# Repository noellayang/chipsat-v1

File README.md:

# ChipSat v1: Solar-Powered CubeSat Power Testbed

ChipSat v1 is a custom 45mm x 45mm PCB I built to test how firmware power-management decisions affect the actual current draw of a small satellite-style system. It was developed alongside my power budget work for the Duke Solar Sail project.

## What this is

The goal was not to reproduce flight hardware exactly. Instead, I wanted a physical testbed where I could keep the hardware fixed and measure how much the power draw changed as I switched between different firmware schedules.

The board includes:

* ESP32-C3-MINI-1 MCU with native USB
* Solar input and Li-ion charging using the BQ25185
* Two INA219 current and voltage monitors: one on the solar input and one on the main system rail
* ICM-42688-P 6-axis IMU over SPI
* VEML7700 ambient light sensor
* Switchable `+3V3_SENS` rail for the sensor domain
* 36Ω switched load behind a solder jumper to emulate an approximately 300mW ADCS load, comparable to a single magnetorquer actuation
* BLE telemetry using the ESP32-C3 radio as a stand-in for LoRa downlink. I kept the same 780ms transmission window and cadence used in the mission power model (and without attempting to reproduce LoRa RF behavior)

## Repo layout

```text
hardware/         KiCad project: schematic, PCB layout, design rules
manufacturing/    Gerbers, drill files, pick-and-place, fab submission files
images/           Board photos and test figures
docs/             BOM
```

## Firmware power states

| State         | MCU                       | IMU | +3V3_SENS | BLE proxy                           | Mission interpretation                                   |
| ------------- | ------------------------- | --- | --------- | ----------------------------------- | -------------------------------------------------------- |
| Eclipse sleep | Deep sleep between events | Off | Off       | Wake every 30s, advertise for 0.78s | Earth-shadow stress case with nominal telemetry retained |
| Housekeeping  | Active                    | Off | Off       | 0.78s every 30s                     | Scheduling and health checks                             |
| Full sensing  | Active                    | On  | On        | 0.78s every 30s                     | Complete sensing window                                  |

## Results

### Power-state testing

Deep sleep reduced average current by 95.4%.

Each state was run over a representative 30s cycle:

* Eclipse sleep: 2.25mA
* Housekeeping: 48.59 ± 0.10mA
* Full sensing: 50.14 ± 0.11mA

I also tested the switched 36Ω load used to emulate an ADCS event. System current increased from a 26.02mA baseline to 118.48 ± 0.87mA with the load enabled, close to the expected result for an approximately 300mW resistive load.

### BLE telemetry

I held the board in Full Sensing for 60s and enabled BLE advertising for 780ms every 30s.

Across three trials, the baseline stayed at 53.67 ± 0.10mA. During the advertising windows, the INA219 measured short peaks up to 121.5mA.

At this cadence, the radio is active for roughly 2.6% of the cycle. The test helped confirm that the BLE event appears as a short current spike rather than setting the power draw for the full operating period.

### Solar harvesting

I used the solar-side INA219 together with the VEML7700 to compare harvested power against measured illuminance.

Harvested power increased from 3.01 ± 0.68mW at about 1669 lux to 16.77 ± 0.91mW at about 2669 lux.

The lowest-light measurement is close to the practical measurement floor of the INA219 with the 0.1Ω shunt, so that point has noticeably more variation than the higher-light measurements.

## Bring-up notes

A few issues from bring-up ended up being especially useful:

### I2C bus switching

The ESP32-C3 only has one I2C controller, while the board uses two physical I2C buses. Firmware therefore remaps the controller depending on which bus is being accessed.

One issue appeared when I disabled the sensor rail before an I2C transaction had fully completed. This could leave SDA or SCL in the wrong state and break later communication. I fixed it by completing the transaction and releasing the bus before switching off `+3V3_SENS`.

### Low-current measurement floor

Under weak illumination, the solar current became small enough that the INA219 and 0.1Ω shunt were operating near their useful measurement limit. At that point, offset and resolution were large enough for the reported current to occasionally drift around zero.

I kept the data rather than filtering it out, but marked the lowest-light point as being close to the measurement floor.

### BLE stack overhead

One result I did not initially expect was the cost of simply initializing BLE.

Even with advertising disabled, bringing up the BLE stack raised the active current noticeably. Because of this, "advertising off" and "BLE fully deinitialized" are separate power states in the firmware rather than being treated as equivalent.

## Manufacturing

Gerbers, drill files, and the original fab submission files for the 2-layer PCB are included in [`manufacturing/`](manufacturing/).

The KiCad project is the source of truth. If you need outputs for a different board house, regenerate them from:

`hardware/chipsat_v1.kicad_pcb`

## BOM

The full bill of materials, including LCSC part numbers, is available at [`docs/BOM.csv`](docs/BOM.csv).

## Opening the project

KiCad 8 or newer is recommended.

Open:

`hardware/chipsat_v1.kicad_pro`

## License

MIT. See [LICENSE](LICENSE).

The hardware design files are included for reference and reuse. If you build directly on the board design, credit back to this repo is appreciated.

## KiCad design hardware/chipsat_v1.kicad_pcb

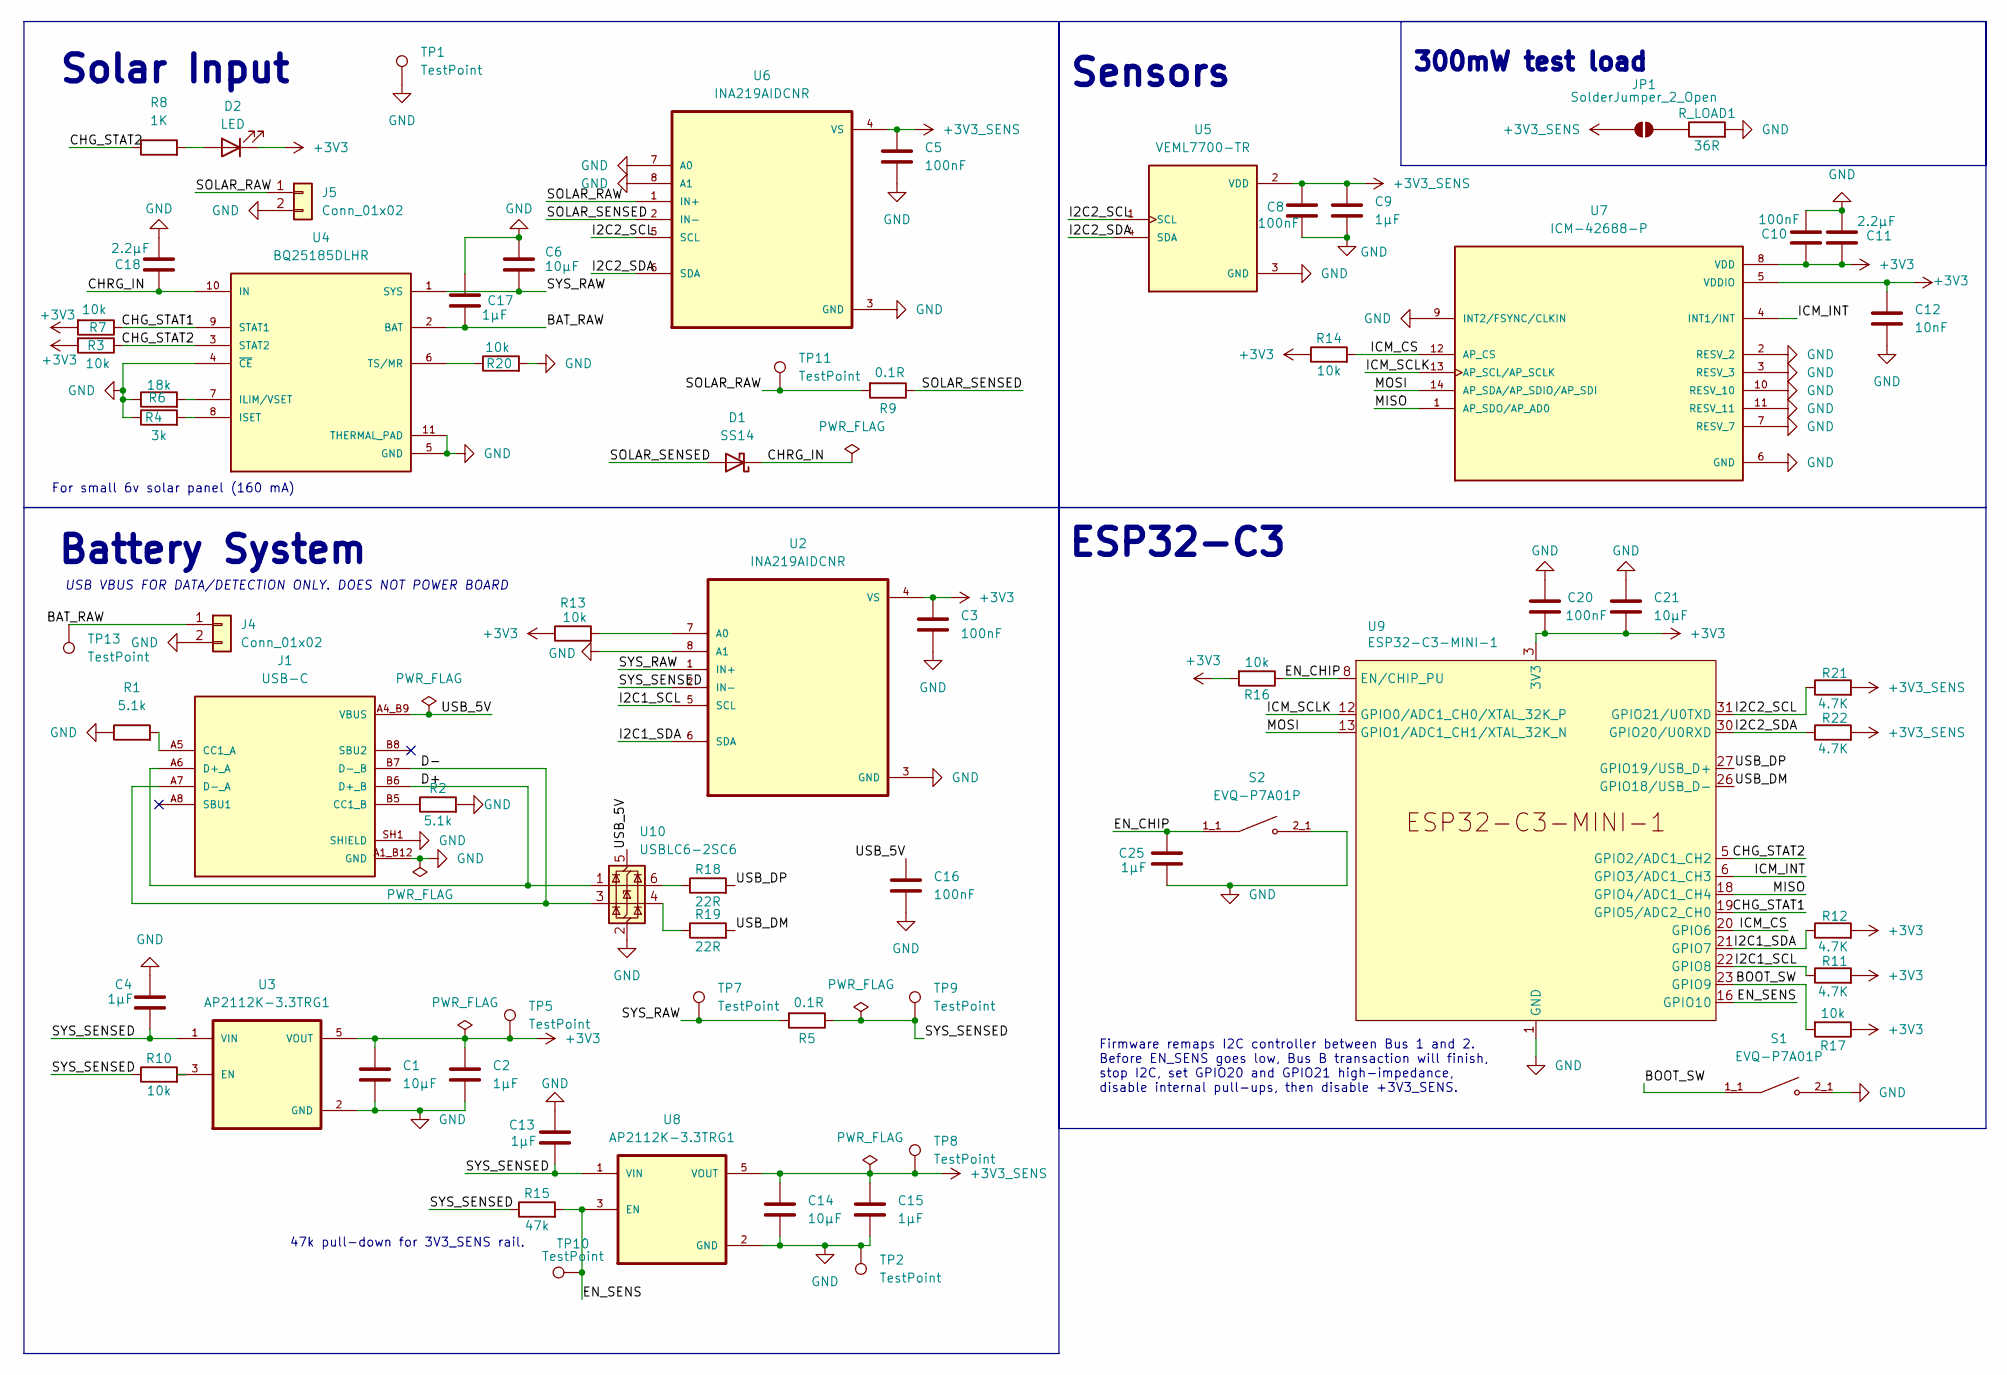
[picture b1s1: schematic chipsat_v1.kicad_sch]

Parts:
C1, C6, C14, C21: 10µF; C_0805_2012Metric; Manufacturer Part Number CL21A106KPFNNNE; LCSC Part # C17024
C2, C4, C9, C13, C15, C17, C25: 1µF; C_0603_1608Metric; Manufacturer Part Number CL10A105KP8NNNC; LCSC Part # C26413
C3, C5, C8, C10, C16, C20: 100nF; C_0603_1608Metric; Manufacturer Part Number CL10B104KB8NNNC; LCSC Part # C1591
C11, C18: 2.2µF; C_0805_2012Metric; Manufacturer Part Number CL21A225KPFNNNE; LCSC Part # C84716
C12: 10nF; C_0603_1608Metric; Manufacturer Part Number CL10B103KB8NNNC; LCSC Part # C1589
D1: SS14; D_SMA; Manufacturer Part Number SS14; LCSC Part # C2480
D2: LED; LED_0603_1608Metric; Manufacturer Part Number KT-0603R; LCSC Part # C2286
J1: USB-C; AMPHENOL_12402012E212A; PARTREV 4; LCSC Part # C5150972
J4, J5: Conn_01x02; JST_XH_B2B-XH-A_1x02_P2.50mm_Vertical; Manufacturer Part Number B2B-XH-A(LF)(SN); LCSC Part # C158012
JP1: SolderJumper_2_Open; SolderJumper-2_P1.3mm_Open_RoundedPad1.0x1.5mm
R1, R2: 5.1k; R_0603_1608Metric; Manufacturer Part Number 0603WAF5101T5E; LCSC Part # C23186
R3, R7, R10, R13, R14, R16, R17, R20: 10k; R_0603_1608Metric; Manufacturer Part Number 0603WAF1002T5E; LCSC Part # C25804
R4: 3k; R_0603_1608Metric; Manufacturer Part Number 0603WAF3001T5E; LCSC Part # C4211
R5, R9: 0.1R; R_1206_3216Metric; Manufacturer Part Number RE1206F1R100; LCSC Part # C46961734
R6: 18k; R_0603_1608Metric; Manufacturer Part Number 0603WAF1802T5E; LCSC Part # C25810
R8: 1K; R_0603_1608Metric; Manufacturer Part Number RC0603FR-071KL; LCSC Part # C22548
R11, R12, R21, R22: 4.7K; R_0603_1608Metric; Manufacturer Part Number 0603WAF4701T5E; LCSC Part # C23162
R15: 47k; R_0603_1608Metric; Manufacturer Part Number 0603WAF4702T5E; LCSC Part # C25819
R18, R19: 22R; R_0603_1608Metric; Manufacturer Part Number 0603WAF220JT5E; LCSC Part # C23345
R_LOAD1: 36R; R_2512_6332Metric; Manufacturer Part Number 25121WF360JT4E; LCSC Part # C190228
S1, S2: EVQ-P7A01P; SW_EVQ-P7A01P; PARTREV 2022.4; LCSC Part # C79167
TP1, TP2, TP5, TP7, TP8, TP9, TP11, TP13: TestPoint; TP_SMD_Round_1.5mm
TP10: TestPoint; TP_SMD_Round_1.2mm
U2, U6: INA219AIDCNR; SOT65P280X145-8N; Manufacturer Part Number INA219AIDCNR; LCSC Part # C87469
U3, U8: AP2112K-3.3TRG1; SOT95P285X140-5N; PARTREV 2-2; LCSC Part # C51118
U4: BQ25185DLHR; IC_BQ25185DLHR; PARTREV OCTOBER 2023; LCSC Part # C19725033
U5: VEML7700-TR; XDCR_VEML7700-TR; PARTREV 1.6; LCSC Part # C504893
U7: ICM-42688-P; PQFN50P300X250X97-14N; PARTREV 1.2; LCSC Part # C1850418
U9: ESP32-C3-MINI-1; Manufacturer Part Number ESP32-C3-MINI-1-N4; LCSC Part # C2838502
U10: USBLC6-2SC6; SOT-23-6; Manufacturer Part Number USBLC6-2SC6; LCSC Part # C7519

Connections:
+3V3: C1.1, C2.2, C3.1, C10.1, C11.1, C12.1, C20.2, C21.2, D2.1 (K), R3.2, R7.2, R11.2, R12.2, R13.1, R14.1, R16.2, R17.1, TP5.1 (1_1), U2.4 (VS), U3.5 (VOUT), U7.5 (VDDIO), U7.8 (VDD), U9.3 (3V3)
+3V3_SENS: C5.1, C8.2, C9.2, C14.2, C15.2, JP1.1 (A), R21.2, R22.2, TP8.1 (1_1), U5.2 (VDD), U6.4 (VS), U8.5 (VOUT)
/BAT_RAW: C17.1, J4.1, TP13.1 (1_1), U4.2 (BAT)
/BOOT_SW: R17.2, S1.1_1, S1.1_2, U9.23 (GPIO9)
/CHG_STAT1: R7.1, U4.9 (STAT1), U9.19 (GPIO5/ADC2_CH0)
/CHG_STAT2: R3.1, R8.1, U4.3 (STAT2), U9.5 (GPIO2/ADC1_CH2)
/CHRG_IN: C18.1, D1.1 (K), U4.10 (IN)
/D+: J1.A6 (D+_A), J1.B6 (D+_B), U10.1 (I/O1)
/D-: J1.A7 (D-_A), J1.B7 (D-_B), U10.3 (I/O2)
/EN_CHIP: C25.2, R16.1, S2.1_1, S2.1_2, U9.8 (EN/CHIP_PU)
/EN_SENS: R15.2, TP10.1 (1_1), U8.3 (EN), U9.16 (GPIO10)
/I2C1_SCL: R11.1, U2.5 (SCL), U9.22 (GPIO8)
/I2C1_SDA: R12.1, U2.6 (SDA), U9.21 (GPIO7)
/I2C2_SCL: R21.1, U5.1 (SCL), U6.5 (SCL), U9.31 (GPIO21/U0TXD)
/I2C2_SDA: R22.1, U5.4 (SDA), U6.6 (SDA), U9.30 (GPIO20/U0RXD)
/ICM_CS: R14.2, U7.12 (AP_CS), U9.20 (GPIO6)
/ICM_INT: U7.4 (INT1/INT), U9.6 (GPIO3/ADC1_CH3)
/ICM_SCLK: U7.13 (AP_SCL/AP_SCLK), U9.12 (GPIO0/ADC1_CH0/XTAL_32K_P)
/MISO: U7.1 (AP_SDO/AP_AD0), U9.18 (GPIO4/ADC1_CH4)
/MOSI: U7.14 (AP_SDA/AP_SDIO/AP_SDI), U9.13 (GPIO1/ADC1_CH1/XTAL_32K_N)
/SOLAR_RAW: J5.1, R9.2, TP11.1 (1_1), U6.1 (IN+)
/SOLAR_SENSED: D1.2 (A), R9.1, U6.2 (IN-)
/SYS_RAW: C6.2, R5.2, TP7.1 (1_1), U2.1 (IN+), U4.1 (SYS)
/SYS_SENSED: C4.1, C13.1, R5.1, R10.1, R15.1, TP9.1 (1_1), U2.2 (IN-), U3.1 (VIN), U8.1 (VIN)
/USB_DM: R19.2, U9.26 (GPIO18/USB_D-)
/USB_DP: R18.2, U9.27 (GPIO19/USB_D+)
GND: C1.2, C2.1, C3.2, C4.2, C5.2, C6.1, C8.1, C9.1, C10.2, C11.2, C12.2, C13.2, C14.1, C15.1, C16.1, C17.2, C18.2, C20.1, C21.1, C25.1, J1.A1_B12 (GND), J1.B1_A12 (GND), J1.SH1 (SHIELD), J1.SH2 (SHIELD), J1.SH3 (SHIELD), J1.SH4 (SHIELD), J4.2, J5.2, R1.1, R2.2, R4.1, R6.1, R20.2, R_LOAD1.2, S1.2_1, S1.2_2, S2.2_1, S2.2_2, TP1.1 (1_1), TP2.1 (1_1), U2.3 (GND), U2.8 (A1), U3.2 (GND), U4.4 (~CE), U4.5 (GND), U4.11 (THERMAL_PAD), U5.3 (GND), U6.3 (GND), U6.7 (A0), U6.8 (A1), U7.2 (RESV_2), U7.3 (RESV_3), U7.6 (GND), U7.7 (RESV_7), U7.9 (INT2/FSYNC/CLKIN), U7.10 (RESV_10), U7.11 (RESV_11), U8.2 (GND), U9.1 (GND), U9.2 (GND), U9.11 (GND), U9.14 (GND), U9.36 (GND), U9.37 (GND), U9.38 (GND), U9.39 (GND), U9.40 (GND), U9.41 (GND), U9.42 (GND), U9.43 (GND), U9.44 (GND), U9.45 (GND), U9.46 (GND), U9.47 (GND), U9.48 (GND), U9.49 (GND), U9.50 (GND), U9.51 (GND), U9.52 (GND), U9.53 (GND), U10.2 (GND)
unnamed: D2.2 (A), R8.2
unnamed: J1.A5 (CC1_A), R1.2
unnamed: J1.B5 (CC1_B), R2.1
unnamed: JP1.2 (B), R_LOAD1.1
unnamed: R18.1, U10.6 (I/O1)
unnamed: R19.1, U10.4 (I/O2)
unnamed: R13.2, U2.7 (A0)
unnamed: R10.2, U3.3 (EN)
unnamed: R6.2, U4.7 (ILIM/VSET)
unnamed: R4.2, U4.8 (ISET)
unnamed: R20.1, U4.6 (TS/MR)
VBUS: C16.2, J1.A4_B9 (VBUS), J1.B4_A9 (VBUS), U10.5 (VBUS)

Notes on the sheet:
ESP32-C3
47k pull-down for 3V3_SENS rail.
Firmware remaps I2C controller between Bus 1 and 2. Before EN_SENS goes low, Bus B transaction will finish, stop I2C, set GPIO20 and GPIO21 high-impedance, disable internal pull-ups, then disable +3V3_SENS.
USB VBUS FOR DATA/DETECTION ONLY. DOES NOT POWER BOARD
300mW test load
Battery System
Solar Input
For small 6v solar panel (160 mA)
Sensors

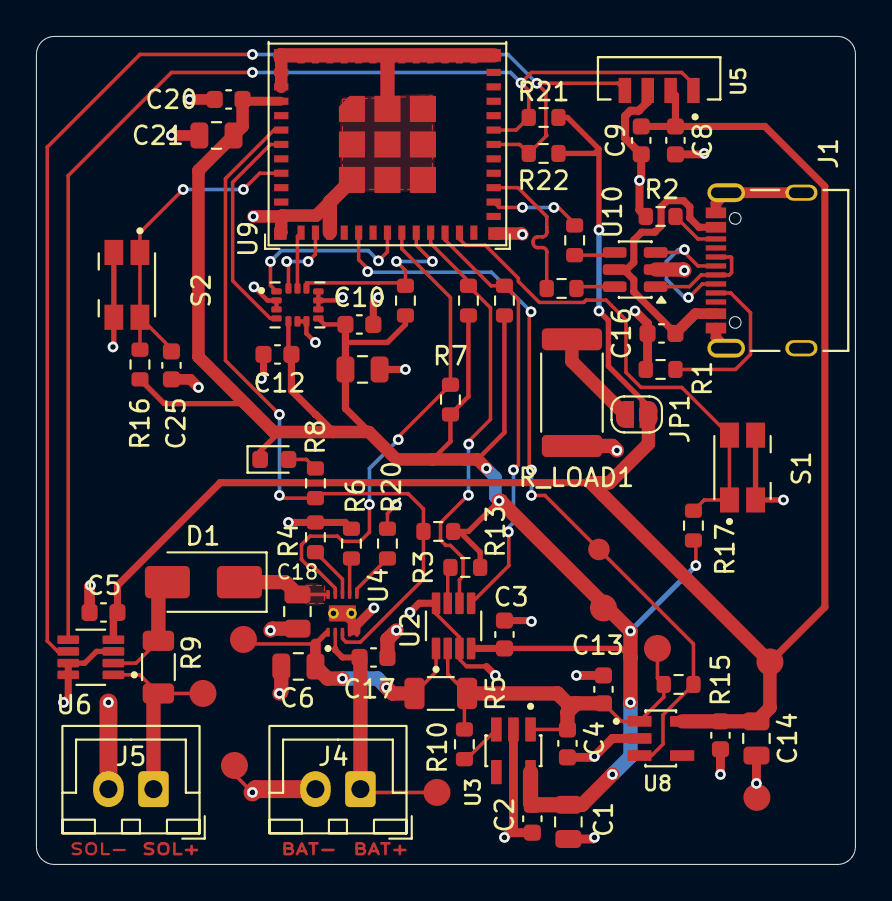
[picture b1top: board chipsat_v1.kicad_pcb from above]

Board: 2 copper layers, 45.5 x 46.0 mm, 69 parts (0 on the bottom side), 39 nets.

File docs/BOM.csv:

"Designator","Qty","Comment","Footprint","LCSC Part #","Manufacturer","Manufacturer Part Number"
"C1,C6,C14,C21","4","10µF","Capacitor_SMD:C_0805_2012Metric","C17024","Samsung Electro-Mechanics","CL21A106KPFNNNE"
"C2,C4,C9,C13,C15,C17,C25","7","1µF","Capacitor_SMD:C_0603_1608Metric","C26413","Samsung Electro-Mechanics","CL10A105KP8NNNC"
"C3,C5,C8,C10,C16,C20","6","100nF","Capacitor_SMD:C_0603_1608Metric","C1591","Samsung Electro-Mechanics","CL10B104KB8NNNC"
"C11,C18","2","2.2µF","Capacitor_SMD:C_0805_2012Metric","C7282443","Murata Electronics","GRM219R61A225KA01D"
"C12","1","10nF","Capacitor_SMD:C_0603_1608Metric","C1589","Samsung Electro-Mechanics","CL10B103KB8NNNC"
"D1","1","SS14","Diode_SMD:D_SMA","C2480","MDD(Microdiode Semiconductor)","SS14"
"D2","1","LED","LED_SMD:LED_0603_1608Metric","C2286","Hubei KENTO Elec","KT-0603R"
"J1","1","USB-C","12402012E212A:AMPHENOL_12402012E212A","C5150972","Amphenol ICC","12402012E212A"
"J4,J5","2","Conn_01x02","Connector_JST:JST_XH_B2B-XH-A_1x02_P2.50mm_Vertical","C19272845","JST","B2B-XH-A"
"R1,R2","2","5.1k","Resistor_SMD:R_0603_1608Metric","C23186","UNI-ROYAL(Uniroyal Elec)","0603WAF5101T5E"
"R3,R7,R10,R13,R14,R16,R17,R20","8","10k","Resistor_SMD:R_0603_1608Metric","C25804","UNI-ROYAL(Uniroyal Elec)","0603WAF1002T5E"
"R4","1","3k","Resistor_SMD:R_0603_1608Metric","C4211","UNI-ROYAL(Uniroyal Elec)","0603WAF3001T5E"
"R5,R9","2","0.1R","Resistor_SMD:R_1206_3216Metric","C46961734","jieerrui","RE1206F1R100"
"R6","1","18k","Resistor_SMD:R_0603_1608Metric","C25810","UNI-ROYAL(Uniroyal Elec)","0603WAF1802T5E"
"R8","1","1K","Resistor_SMD:R_0603_1608Metric","C22548","YAGEO","RC0603FR-071KL"
"R11,R12,R21,R22","4","4.7K","Resistor_SMD:R_0603_1608Metric","C23162","UNI-ROYAL(Uniroyal Elec)","0603WAF4701T5E"
"R15","1","47k","Resistor_SMD:R_0603_1608Metric","C25819","UNI-ROYAL(Uniroyal Elec)","0603WAF4702T5E"
"R18,R19","2","22R","Resistor_SMD:R_0603_1608Metric","C23345","UNI-ROYAL(Uniroyal Elec)","0603WAF220JT5E"
"R_LOAD1","1","36R","Resistor_SMD:R_2512_6332Metric","C190228","UNI-ROYAL(Uniroyal Elec)","25121WF360JT4E"
"S1,S2","2","EVQ-P7A01P","EVQ-P7A01P:SW_EVQ-P7A01P","C79167","PANASONIC","EVQP7A01P"
"U2,U6","2","INA219AIDCNR","INA219AIDCNR:SOT65P280X145-8N","C87469","Texas Instruments","INA219AIDCNR"
"U3,U8","2","AP2112K-3.3TRG1","AP2112K-3.3TRG1:SOT95P285X140-5N","C51118","Diodes Inc.","AP2112K-3.3TRG1"
"U4","1","BQ25185DLHR","BQ25185DLHR:IC_BQ25185DLHR","C19725033","Texas Instruments","BQ25185DLHR"
"U5","1","VEML7700-TR","VEML7700-TR:XDCR_VEML7700-TR","C504893","Vishay Intertech","VEML7700-TR"
"U7","1","ICM-42688-P","ICM-42688-P:PQFN50P300X250X97-14N","C1850418","TDK InvenSense","ICM-42688-P"
"U9","1","ESP32-C3-MINI-1","PCM_Espressif:ESP32-C3-MINI-1","C2838502","Espressif Systems","ESP32-C3-MINI-1-N4"
"U10","1","USBLC6-2SC6","Package_TO_SOT_SMD:SOT-23-6","C7519","STMicroelectronics","USBLC6-2SC6"
